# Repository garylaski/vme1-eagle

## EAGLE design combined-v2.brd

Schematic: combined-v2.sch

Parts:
3V3_D1, 9VDD1: SMD2; SMD1,27-2,54
10KPOT1_PAN1, 10KPOT1_PAN2, 10KPOT1_PAN3, 10KPOT1_PAN4, 10POT1_COMP1, 10POT1_COMP2, 10POT1_COMP3, 10POT1_COMP5, 10POT2_COMP1, 10POT2_COMP2, 10POT2_COMP3, 10POT2_COMP5: MCP4131-503E/SN; SOIC127P599X175-8N
100POT1_COMP1, 100POT1_COMP2, 100POT1_COMP3, 100POT1_COMP5: MCP42100-I/P; DIP254P762X432-14
200POT1_COMP1, 200POT2_COMP1: MAX5419NETA+; SON65P300X300X80-9N
200POT1_COMP2, 200POT2_COMP2: MAX5419META+; SON65P300X300X80-9N
200POT1_COMP3, 200POT2_COMP3: MAX5419PETAT; SON65P300X300X80-9N
200POT1_COMP5, 200POT2_COMP5: MAX5419LETA+; SON65P300X300X80-9N
BCK_ADC1: SMD2; SMD1,27-2,54
C2, C5, C6, C8, C24, C25, C26, C27, C28, C29, C30, C31, C32, C34, C35, C36, C37, C39, C43, C46, C49, C55, C69, C71, C77, C78, C79, C80, C81, C82, C83, C84, C119, C120, C121, C122, C123, C124, C125, C126, C127, C129, C130, C131, C132, C134: 10uF; C0402
C3, C4, C33, C38, C68, C70, C73, C128, C133: 0.1uF; C0402
C7, C9, C22, C23, C103, C104, C117, C118: 0.047uF; C0402
C10, C11, C14, C15, C16, C17, C20, C21, C105, C106, C109, C110, C111, C112, C115, C116: 0.01uF; C0402
C12, C13, C18, C19, C107, C108, C113, C114: 0.068uF; C0402
C42, C45, C48, C54: 680pF; C0402
C44, C47, C50, C56: 1.5uF; C0402
C72, C74: 1uF; C0402
C75, C76: 15pF; C0402
CE_EQ1, CE_EQ2: SMD2; SMD1,27-2,54
CLK_ADC1: SMD2; SMD1,27-2,54
CS3, CS4, CS5, CS6: SMD2; SMD1,27-2,54
D2, D3, D4, D5, D16, D17, D18, D19, D20, D21, D22, D23, D24, D25, D26, D27, D28, D29, D30, D31, D32, D33, D34, D35, D36, D37, D38, D39, D40, D41, D42, D43, D44, D45, D46, D47, D48, D60, D61, D62, D63, D64, D65, D66, D67, D68, D69, D70: 1N4148W-TP; SOD123
DOUT_ADC1: SMD2; SMD1,27-2,54
GND1, GND2, GND3, GND5: SMD5; SMD2,54-5,08
GND4, GND6: SMD2; SMD1,27-2,54
GNDL1: SMD5; SMD2,54-5,08
GNDR1: SMD5; SMD2,54-5,08
IC2: PCM1865DBT; TSSOP-30
IN_COMP1, IN_COMP2, IN_COMP3, IN_COMP5: SMD5; SMD2,54-5,08
LRCK_ADC1: SMD2; SMD1,27-2,54
MUX2, MUX3: SMD2; SMD1,27-2,54
OPAMP1_COMP1, OPAMP1_COMP2, OPAMP1_COMP3, OPAMP1_COMP5, OPAMP1_MIX1, OPAMP1_PAN1, OPAMP1_PAN2, OPAMP1_PAN3, OPAMP1_PAN4, OPAMP2_COMP1, OPAMP2_COMP2, OPAMP2_COMP3, OPAMP2_COMP5, OPAMP3_COMP1, OPAMP3_COMP2, OPAMP3_COMP3, OPAMP3_COMP5, OPAMP4_COMP1, OPAMP4_COMP2, OPAMP4_COMP3, OPAMP4_COMP5: LM4562MAX/NOPB; SOIC127P599X175-8N
OUTL_MIX1: SMD5; SMD2,54-5,08
OUTR_MIX1: SMD5; SMD2,54-5,08
PAD1, PAD2, PAD3, PAD4, PAD5, PAD6, PAD7, PAD8, PAD9, PAD10, PAD11, PAD12, PAD13, PAD14, PAD15, PAD16: SMD2; SMD1,27-2,54
R5, R8, R9, R12, R14, R19, R21, R32, R34, R41, R42, R47, R49, R56, R57, R72, R74, R76, R80, R86, R88, R92, R101, R105, R110, R119, R123, R128, R155, R159, R164: 10k; R0402
R6, R15, R68, R82: 1M; R0402
R7, R10, R11, R13, R16, R17, R18, R20, R31, R33, R35, R36, R37, R38, R39, R40, R43, R46, R48, R50, R51, R52, R53, R54, R55, R58, R69, R70, R71, R73, R83, R84, R85, R87: 5k; R0402
R22: 17k; R0402
R44, R59: 50k; R0402
R45, R60, R65, R97, R115, R151: 1k; R0402
R63, R67, R75, R77, R78, R79, R89, R90, R91, R93, R94, R95, R99, R100, R102, R103, R104, R107, R108, R109, R111, R112, R113, R117, R118, R120, R121, R122, R125, R126, R127, R129, R130, R149, R153, R154, R156, R157, R158, R161, R162, R163, R165, R166: 100k; R0402
R64, R66, R96, R98, R114, R116, R150, R152: 470k; R0402
R81, R106, R124, R160: 20k; R0402
SCK1: SMD2; SMD1,27-2,54
SCL1, SCL2: SMD2; SMD1,27-2,54
SDA1, SDA2: SMD2; SMD1,27-2,54
SDI/O1: SMD2; SMD1,27-2,54
U2: LM4562MAX/NOPB; SOIC127P599X175-8N
U3, U4, U5, U11: TMUX1204DGSR; SOP50P490X110-10N
U$1, U$3: LC75281E; QFP80P1720X1720X270-64N
Y2: ECS-245.7-20-3X-EN-TR; XTAL_ECS-245.7-20-3X-EN-TR

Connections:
3V3A: C70.1, C71.1, IC2.8 (AVDD), U2.1 (OUT_A), U2.2 (NEG_A)
3V3D: C68.1, C69.1, IC2.13 (DVDD), IC2.14 (IOVDD)
+3V3: 3V3_D1.1, U3.5 (EN), U3.6 (VDD), U4.5 (EN), U4.6 (VDD), U5.5 (EN), U5.6 (VDD), U11.5 (EN), U11.6 (VDD)
BCK_ADC: BCK_ADC1.1, IC2.17 (BCK)
CLK_ADC: CLK_ADC1.1, IC2.15 (SCKI)
CS: CS6.1, U11.8 (D)
CS0: CS3.1, U3.8 (D)
CS0_COMP1: 100POT1_COMP1.1 (~CS), U3.2 (S1)
CS0_COMP2: 100POT1_COMP3.1 (~CS), U3.9 (S2)
CS0_COMP3: 100POT1_COMP2.1 (~CS), U3.4 (S3)
CS0_COMP4: 100POT1_COMP5.1 (~CS), U3.7 (S4)
CS1: CS4.1, U5.8 (D)
CS1_COMP1: 10POT1_COMP1.1 (!CS), U5.2 (S1)
CS1_COMP2: 10POT1_COMP3.1 (!CS), U5.9 (S2)
CS1_COMP3: 10POT1_COMP2.1 (!CS), U5.4 (S3)
CS1_COMP4: 10POT1_COMP5.1 (!CS), U5.7 (S4)
CS2: CS5.1, U4.8 (D)
CS2_COMP1: 10POT2_COMP1.1 (!CS), U4.2 (S1)
CS2_COMP2: 10POT2_COMP3.1 (!CS), U4.9 (S2)
CS2_COMP3: 10POT2_COMP2.1 (!CS), U4.4 (S3)
CS2_COMP4: 10POT2_COMP5.1 (!CS), U4.7 (S4)
CS_PAN1: 10KPOT1_PAN1.1 (!CS), U11.2 (S1)
CS_PAN2: 10KPOT1_PAN3.1 (!CS), U11.9 (S2)
CS_PAN3: 10KPOT1_PAN2.1 (!CS), U11.4 (S3)
CS_PAN4: 10KPOT1_PAN4.1 (!CS), U11.7 (S4)
DOUT_ADC: DOUT_ADC1.1, IC2.18 (DOUT)
EQ1_CE1: CE_EQ1.1, U$1.27 (CE)
EQ2_CE3: CE_EQ2.1, U$3.27 (CE)
GND: 10KPOT1_PAN1.4 (VSS), 10KPOT1_PAN2.4 (VSS), 10KPOT1_PAN3.4 (VSS), 10KPOT1_PAN4.4 (VSS), 10POT1_COMP1.4 (VSS), 10POT1_COMP2.4 (VSS), 10POT1_COMP3.4 (VSS), 10POT1_COMP5.4 (VSS), 10POT2_COMP1.4 (VSS), 10POT2_COMP2.4 (VSS), 10POT2_COMP3.4 (VSS), 10POT2_COMP5.4 (VSS), 100POT1_COMP1.4 (VSS), 100POT1_COMP2.4 (VSS), 100POT1_COMP3.4 (VSS), 100POT1_COMP5.4 (VSS), 200POT1_COMP1.5 (GND), 200POT1_COMP1.9 (EPAD), 200POT1_COMP2.5 (GND), 200POT1_COMP2.9 (EPAD), 200POT1_COMP3.5 (GND), 200POT1_COMP3.9 (EPAD), 200POT1_COMP5.5 (GND), 200POT1_COMP5.9 (EPAD), 200POT2_COMP1.4 (A0), 200POT2_COMP1.5 (GND), 200POT2_COMP1.9 (EPAD), 200POT2_COMP2.4 (A0), 200POT2_COMP2.5 (GND), 200POT2_COMP2.9 (EPAD), 200POT2_COMP3.4 (A0), 200POT2_COMP3.5 (GND), 200POT2_COMP3.9 (EPAD), 200POT2_COMP5.4 (A0), 200POT2_COMP5.5 (GND), 200POT2_COMP5.9 (EPAD), C28.2, C39.2, C68.2, C69.2, C70.2, C71.2, C72.2, C73.2, C74.2, C75.2, C76.2, C123.2, C134.2, GND1.1, GND2.1, GND3.1, GND4.1, GND5.1, GND6.1, GNDL1.1, GNDR1.1, IC2.7 (AGND), IC2.12 (DGND), IC2.25 (MS/AD), OPAMP1_COMP1.4 (V-), OPAMP1_COMP2.4 (V-), OPAMP1_COMP3.4 (V-), OPAMP1_COMP5.4 (V-), OPAMP1_MIX1.4 (V-), OPAMP1_PAN1.4 (V-), OPAMP1_PAN2.4 (V-), OPAMP1_PAN3.4 (V-), OPAMP1_PAN4.4 (V-), OPAMP2_COMP1.4 (V-), OPAMP2_COMP2.4 (V-), OPAMP2_COMP3.4 (V-), OPAMP2_COMP5.4 (V-), OPAMP3_COMP1.4 (V-), OPAMP3_COMP2.4 (V-), OPAMP3_COMP3.4 (V-), OPAMP3_COMP5.4 (V-), OPAMP4_COMP1.4 (V-), OPAMP4_COMP2.4 (V-), OPAMP4_COMP3.4 (V-), OPAMP4_COMP5.4 (V-), R5.1, R9.1, U2.4 (V-), U3.3 (GND), U4.3 (GND), U5.3 (GND), U11.3 (GND), U$1.21 (V_SS), U$1.28 (TEST), U$3.21 (V_SS), U$3.28 (TEST)
H1_COMP1: 200POT1_COMP1.8 (H), 200POT2_COMP1.8 (H), C44.1, OPAMP1_COMP1.6 (NEG_B), R66.1
H1_COMP2: 200POT1_COMP3.8 (H), 200POT2_COMP3.8 (H), C50.1, OPAMP1_COMP3.6 (NEG_B), R116.1
H1_COMP3: 200POT1_COMP2.8 (H), 200POT2_COMP2.8 (H), C47.1, OPAMP1_COMP2.6 (NEG_B), R98.1
H1_COMP4: 200POT1_COMP5.8 (H), 200POT2_COMP5.8 (H), C56.1, OPAMP1_COMP5.6 (NEG_B), R152.1
IN_COMP1: C43.2, IN_COMP1.1
IN_COMP2: C49.2, IN_COMP3.1
IN_COMP3: C46.2, IN_COMP2.1
IN_COMP4: C55.2, IN_COMP5.1
L1_COMP1: 200POT1_COMP1.6 (L), 200POT1_COMP1.7 (W), D19.1
L1_COMP2: 200POT1_COMP3.6 (L), 200POT1_COMP3.7 (W), D41.1
L1_COMP3: 200POT1_COMP2.6 (L), 200POT1_COMP2.7 (W), D30.1
L1_COMP4: 200POT1_COMP5.6 (L), 200POT1_COMP5.7 (W), D63.1
L2_COMP1: 200POT2_COMP1.6 (L), 200POT2_COMP1.7 (W), R94.2
L2_COMP2: 200POT2_COMP3.6 (L), 200POT2_COMP3.7 (W), R130.2
L2_COMP3: 200POT2_COMP2.6 (L), 200POT2_COMP2.7 (W), R112.2
L2_COMP4: 200POT2_COMP5.6 (L), 200POT2_COMP5.7 (W), R166.2
LRCK_ADC: IC2.16 (LRCK), LRCK_ADC1.1
MUX0: MUX2.1, U3.1 (A0), U4.1 (A0), U5.1 (A0), U11.1 (A0)
MUX1: MUX3.1, U3.10 (A1), U4.10 (A1), U5.10 (A1), U11.10 (A1)
unnamed: C2.2, R6.2, R7.2, R10.2
unnamed: C5.2, R15.2, R16.2, R17.2
unnamed: C7.1, U$1.1 (LLC1)
unnamed: C10.1, U$1.6 (LLMC1)
unnamed: C11.1, U$1.7 (LLMC4)
unnamed: C12.1, U$1.11 (LHMC1)
unnamed: C3.1, R45.2
unnamed: R32.1, R35.2, R39.2
unnamed: R32.2, R34.2, R41.2, R42.2, R43.1
unnamed: R31.2, R38.1, R42.1
unnamed: R33.2, R37.1, R41.1
unnamed: C13.1, U$1.12 (LHMC4)
unnamed: C14.1, U$1.16 (LHC1)
unnamed: C15.1, U$1.17 (LHC4)
unnamed: C16.1, U$1.32 (RHC4)
unnamed: C17.1, U$1.33 (RHC1)
unnamed: R34.1, R36.1, R40.2
unnamed: C4.1, R60.2
unnamed: R47.1, R50.2, R54.2
unnamed: R47.2, R49.2, R56.2, R57.2, R58.1
unnamed: R46.2, R53.1, R57.1
unnamed: R48.2, R52.1, R56.1
unnamed: R49.1, R51.1, R55.2
unnamed: C18.1, U$1.37 (RHMC4)
unnamed: C6.2, R68.2, R69.2, R70.2
unnamed: C19.1, U$1.38 (RHMC1)
unnamed: C8.2, R82.2, R83.2, R84.2
unnamed: C20.1, U$1.42 (RLMC4)
unnamed: C21.1, U$1.43 (RLMC1)
unnamed: C22.1, U$1.47 (RLC4)
unnamed: C23.1, U$1.48 (RLC1)
unnamed: C7.2, U$1.64 (LLC2)
unnamed: C9.2, C24.2, U$1.3 (LLC3)
unnamed: C24.1, U$1.4 (LLC5)
unnamed: C25.1, U$1.9 (LLMC5)
unnamed: C26.1, U$1.14 (LHMC5)
unnamed: C27.1, U$1.19 (LHC5)
unnamed: C28.1, C39.1, U$1.23 (V_REF)
unnamed: C29.1, U$1.30 (RHC5)
unnamed: C30.1, U$1.35 (RHMC5)
unnamed: C31.1, U$1.40 (RLMC5)
unnamed: C32.1, U$1.45 (RLC5)
unnamed: C33.1, U$1.50 (ROUT)
unnamed: C34.1, U$1.52 (RBOOS2)
unnamed: C35.1, U$1.55 (RCUT2)
unnamed: C36.1, U$1.59 (LCUT1)
unnamed: C37.1, U$1.62 (LBOOS1)
unnamed: C38.1, U$1.63 (LOUT)
unnamed: C10.2, U$1.5 (LLMC2)
unnamed: C11.2, C25.2, U$1.8 (LLMC3)
unnamed: C12.2, U$1.10 (LHMC2)
unnamed: C13.2, C26.2, U$1.13 (LHMC3)
unnamed: C14.2, U$1.15 (LHC2)
unnamed: C15.2, C27.2, U$1.18 (LHC3)
unnamed: C16.2, C29.2, U$1.31 (RHC3)
unnamed: C17.2, U$1.34 (RHC2)
unnamed: C18.2, C30.2, U$1.36 (RHMC3)
unnamed: C19.2, U$1.39 (RHMC2)
unnamed: C20.2, C31.2, U$1.41 (RLMC3)
unnamed: C21.2, U$1.44 (RLMC2)
unnamed: C22.2, C32.2, U$1.46 (RLC3)
unnamed: C23.2, U$1.49 (RLC2)
unnamed: C34.2, U$1.51 (RBOOS1)
unnamed: C35.2, U$1.54 (RCUT1)
unnamed: C36.2, U$1.58 (LCUT2)
unnamed: C37.2, U$1.61 (LBOOS2)
unnamed: C9.1, U$1.2 (LLC4)
unnamed: R9.2, R22.2, U2.3 (POS_A)
unnamed: R5.2, R8.2, U2.5 (POS_B)
unnamed: D16.2, D17.1
unnamed: D21.2, D22.1
unnamed: D20.2, D21.1
unnamed: C43.1, R91.2
unnamed: D24.2, D25.1
unnamed: D23.2, D24.1
unnamed: D27.2, D28.1
unnamed: D32.2, D33.1
unnamed: D31.2, D32.1
unnamed: C46.1, R109.2
unnamed: D35.2, D36.1
unnamed: D34.2, D35.1
unnamed: D38.2, D39.1
unnamed: D43.2, D44.1
unnamed: D42.2, D43.1
unnamed: C49.1, R127.2
unnamed: D46.2, D47.1
unnamed: D45.2, D46.1
unnamed: D60.2, D61.1
unnamed: D65.2, D66.1
unnamed: D64.2, D65.1
unnamed: C55.1, R163.2
unnamed: D68.2, D69.1
unnamed: D67.2, D68.1
unnamed: C72.1, IC2.6 (VREF)
unnamed: C73.1, C74.1, IC2.11 (LDO)
unnamed: C75.1, IC2.9 (XO), Y2.2
unnamed: C76.1, IC2.10 (XI), Y2.1
unnamed: C84.2, IC2.1 (VINL2/VIN1M)
unnamed: C77.2, IC2.2 (VINR2/VIN2M)
unnamed: C103.1, U$3.1 (LLC1)
unnamed: C105.1, U$3.6 (LLMC1)
unnamed: C106.1, U$3.7 (LLMC4)
unnamed: C81.2, IC2.3 (VINL1/VIN1P)
unnamed: C107.1, U$3.11 (LHMC1)
unnamed: C78.2, IC2.4 (VINR1/VIN2P)
unnamed: C79.2, IC2.29 (VINL3/VIN4P)
unnamed: C83.2, IC2.28 (VINR4/VIN3M)
unnamed: C80.2, IC2.27 (VINL4/VIN4M)
unnamed: C108.1, U$3.12 (LHMC4)
unnamed: C109.1, U$3.16 (LHC1)
unnamed: C110.1, U$3.17 (LHC4)
unnamed: C111.1, U$3.32 (RHC4)
unnamed: C112.1, U$3.33 (RHC1)
unnamed: C113.1, U$3.37 (RHMC4)
unnamed: C114.1, U$3.38 (RHMC1)
unnamed: C115.1, U$3.42 (RLMC4)
unnamed: C116.1, U$3.43 (RLMC1)
unnamed: C117.1, U$3.47 (RLC4)
unnamed: C118.1, U$3.48 (RLC1)
unnamed: C103.2, U$3.64 (LLC2)
unnamed: C104.2, C119.2, U$3.3 (LLC3)
unnamed: C119.1, U$3.4 (LLC5)
unnamed: C120.1, U$3.9 (LLMC5)
unnamed: C121.1, U$3.14 (LHMC5)
unnamed: C122.1, U$3.19 (LHC5)
unnamed: C123.1, C134.1, U$3.23 (V_REF)
unnamed: C124.1, U$3.30 (RHC5)
unnamed: C125.1, U$3.35 (RHMC5)
unnamed: C126.1, U$3.40 (RLMC5)
unnamed: C127.1, U$3.45 (RLC5)
unnamed: C128.1, U$3.50 (ROUT)
unnamed: C129.1, U$3.52 (RBOOS2)
unnamed: C130.1, U$3.55 (RCUT2)
unnamed: C131.1, U$3.59 (LCUT1)
unnamed: C132.1, U$3.62 (LBOOS1)
unnamed: C133.1, U$3.63 (LOUT)
unnamed: C105.2, U$3.5 (LLMC2)
unnamed: C106.2, C120.2, U$3.8 (LLMC3)
unnamed: C107.2, U$3.10 (LHMC2)
unnamed: C108.2, C121.2, U$3.13 (LHMC3)
unnamed: C109.2, U$3.15 (LHC2)
unnamed: C110.2, C122.2, U$3.18 (LHC3)
unnamed: C111.2, C124.2, U$3.31 (RHC3)
unnamed: C112.2, U$3.34 (RHC2)
unnamed: C113.2, C125.2, U$3.36 (RHMC3)
unnamed: C114.2, U$3.39 (RHMC2)
unnamed: C115.2, C126.2, U$3.41 (RLMC3)
unnamed: C116.2, U$3.44 (RLMC2)
unnamed: C117.2, C127.2, U$3.46 (RLC3)
unnamed: C118.2, U$3.49 (RLC2)
unnamed: C129.2, U$3.51 (RBOOS1)
unnamed: C130.2, U$3.54 (RCUT1)
unnamed: C131.2, U$3.58 (LCUT2)
unnamed: C132.2, U$3.61 (LBOOS2)
unnamed: C104.1, U$3.2 (LLC4)
unnamed: C82.2, IC2.30 (VINR3/VIN3P)
unnamed: C42.1, D17.2, D18.1, D25.2, R65.1, R89.2
unnamed: C48.1, D39.2, D40.1, D47.2, R115.1, R125.2
unnamed: C45.1, D28.2, D29.1, D36.2, R97.1, R107.2
unnamed: C54.1, D61.2, D62.1, D69.2, R151.1, R161.2
NEG_A1_COMP1: C42.2, D16.1, D18.2, OPAMP1_COMP1.2 (NEG_A), R63.2
NEG_A1_COMP2: C48.2, D38.1, D40.2, OPAMP1_COMP3.2 (NEG_A), R113.2
NEG_A1_COMP3: C45.2, D27.1, D29.2, OPAMP1_COMP2.2 (NEG_A), R95.2
NEG_A1_COMP4: C54.2, D60.1, D62.2, OPAMP1_COMP5.2 (NEG_A), R149.2
NEG_A2_COMP1: OPAMP2_COMP1.2 (NEG_A), R67.2, R75.1
NEG_A2_COMP2: OPAMP2_COMP3.2 (NEG_A), R117.2, R118.1
NEG_A2_COMP3: OPAMP2_COMP2.2 (NEG_A), R99.2, R100.1
NEG_A2_COMP4: OPAMP2_COMP5.2 (NEG_A), R153.2, R154.1
NEG_A3_COMP1: OPAMP3_COMP1.2 (NEG_A), R77.1, R78.2
NEG_A3_COMP2: OPAMP3_COMP3.2 (NEG_A), R120.1, R121.2
NEG_A3_COMP3: OPAMP3_COMP2.2 (NEG_A), R102.1, R103.2
NEG_A3_COMP4: OPAMP3_COMP5.2 (NEG_A), R156.1, R157.2
NEG_A4_COMP1: OPAMP4_COMP1.2 (NEG_A), R79.2, R80.2
NEG_A4_COMP2: OPAMP4_COMP3.2 (NEG_A), R122.2, R123.2
NEG_A4_COMP3: OPAMP4_COMP2.2 (NEG_A), R104.2, R105.2
NEG_A4_COMP4: OPAMP4_COMP5.2 (NEG_A), R158.2, R159.2
NEG_A_MIX: OPAMP1_MIX1.2 (NEG_A), R43.2, R44.1
NEG_A_PAN1: OPAMP1_PAN1.2 (NEG_A), R71.1, R74.1
NEG_A_PAN2: OPAMP1_PAN3.2 (NEG_A), R85.1, R88.1
NEG_A_PAN3: OPAMP1_PAN2.2 (NEG_A), R11.1, R14.1
NEG_A_PAN4: OPAMP1_PAN4.2 (NEG_A), R18.1, R21.1
NEG_B2_COMP1: OPAMP2_COMP1.6 (NEG_B), OPAMP2_COMP1.7 (OUT_B), R93.2
NEG_B2_COMP2: OPAMP2_COMP3.6 (NEG_B), OPAMP2_COMP3.7 (OUT_B), R129.2
NEG_B2_COMP3: OPAMP2_COMP2.6 (NEG_B), OPAMP2_COMP2.7 (OUT_B), R111.2
NEG_B2_COMP4: OPAMP2_COMP5.6 (NEG_B), OPAMP2_COMP5.7 (OUT_B), R165.2
NEG_B3_COMP1: OPAMP3_COMP1.6 (NEG_B), R89.1, R90.2
NEG_B3_COMP2: OPAMP3_COMP3.6 (NEG_B), R125.1, R126.2
NEG_B3_COMP3: OPAMP3_COMP2.6 (NEG_B), R107.1, R108.2
NEG_B3_COMP4: OPAMP3_COMP5.6 (NEG_B), R161.1, R162.2
NEG_B4_COMP1: 100POT1_COMP1.5 (PB1), OPAMP4_COMP1.6 (NEG_B), R81.2
NEG_B4_COMP2: 100POT1_COMP3.5 (PB1), OPAMP4_COMP3.6 (NEG_B), R124.2
NEG_B4_COMP3: 100POT1_COMP2.5 (PB1), OPAMP4_COMP2.6 (NEG_B), R106.2
NEG_B4_COMP4: 100POT1_COMP5.5 (PB1), OPAMP4_COMP5.6 (NEG_B), R160.2
NEG_B_MIX: OPAMP1_MIX1.6 (NEG_B), R58.2, R59.1
NEG_B_PAN1: OPAMP1_PAN1.6 (NEG_B), R72.2, R73.2
NEG_B_PAN2: OPAMP1_PAN3.6 (NEG_B), R86.2, R87.2
NEG_B_PAN3: OPAMP1_PAN2.6 (NEG_B), R12.2, R13.2
NEG_B_PAN4: OPAMP1_PAN4.6 (NEG_B), R19.2, R20.2
OUT1_EQ1: C6.1, C33.2, PAD16.1
OUT1_EQ2: C5.1, C128.2, PAD14.1
OUT2_EQ1: C8.1, C38.2, PAD15.1
OUT2_EQ2: C2.1, C133.2, PAD13.1
OUTL_MIX1: C3.2, OUTL_MIX1.1
OUTL_PAN1: C79.1, OPAMP1_PAN1.1 (OUT_A), PAD3.1, R55.1, R74.2
OUTL_PAN2: C80.1, OPAMP1_PAN3.1 (OUT_A), PAD5.1, R31.1, R88.2
OUTL_PAN3: C78.1, OPAMP1_PAN2.1 (OUT_A), PAD1.1, R14.2, R46.1
OUTL_PAN4: C84.1, OPAMP1_PAN4.1 (OUT_A), PAD7.1, R21.2, R40.1
OUTR_MIX1: C4.2, OUTR_MIX1.1
OUTR_PAN1: C82.1, OPAMP1_PAN1.7 (OUT_B), PAD6.1, R33.1, R72.1
OUTR_PAN2: C83.1, OPAMP1_PAN3.7 (OUT_B), PAD4.1, R54.1, R86.1
OUTR_PAN3: C81.1, OPAMP1_PAN2.7 (OUT_B), PAD8.1, R12.1, R39.1
OUTR_PAN4: C77.1, OPAMP1_PAN4.7 (OUT_B), PAD2.1, R19.1, R48.1
OUT_A1_COMP1: OPAMP1_COMP1.1 (OUT_A), R65.2
OUT_A1_COMP2: OPAMP1_COMP3.1 (OUT_A), R115.2
OUT_A1_COMP3: OPAMP1_COMP2.1 (OUT_A), R97.2
OUT_A1_COMP4: OPAMP1_COMP5.1 (OUT_A), R151.2
OUT_A2_COMP1: 100POT1_COMP1.10 (PB0), OPAMP2_COMP1.1 (OUT_A), R75.2
OUT_A2_COMP2: 100POT1_COMP3.10 (PB0), OPAMP2_COMP3.1 (OUT_A), R118.2
OUT_A2_COMP3: 100POT1_COMP2.10 (PB0), OPAMP2_COMP2.1 (OUT_A), R100.2
OUT_A2_COMP4: 100POT1_COMP5.10 (PB0), OPAMP2_COMP5.1 (OUT_A), R154.2
OUT_A3_COMP1: D26.2, OPAMP3_COMP1.1 (OUT_A)
OUT_A3_COMP2: D48.2, OPAMP3_COMP3.1 (OUT_A)
OUT_A3_COMP3: D37.2, OPAMP3_COMP2.1 (OUT_A)
OUT_A3_COMP4: D70.2, OPAMP3_COMP5.1 (OUT_A)
OUT_A4_COMP1: OPAMP4_COMP1.1 (OUT_A), OPAMP4_COMP1.5 (POS_B), R78.1, R79.1
OUT_A4_COMP2: OPAMP4_COMP3.1 (OUT_A), OPAMP4_COMP3.5 (POS_B), R121.1, R122.1
OUT_A4_COMP3: OPAMP4_COMP2.1 (OUT_A), OPAMP4_COMP2.5 (POS_B), R103.1, R104.1
OUT_A4_COMP4: OPAMP4_COMP5.1 (OUT_A), OPAMP4_COMP5.5 (POS_B), R157.1, R158.1
OUT_A_MIX: OPAMP1_MIX1.1 (OUT_A), R44.2, R45.1
OUT_B1_COMP1: D19.2, OPAMP1_COMP1.7 (OUT_B)
OUT_B1_COMP2: D41.2, OPAMP1_COMP3.7 (OUT_B)
OUT_B1_COMP3: D30.2, OPAMP1_COMP2.7 (OUT_B)
OUT_B1_COMP4: D63.2, OPAMP1_COMP5.7 (OUT_B)
OUT_B3_COMP1: D20.1, OPAMP3_COMP1.7 (OUT_B), R90.1
OUT_B3_COMP2: D42.1, OPAMP3_COMP3.7 (OUT_B), R126.1
OUT_B3_COMP3: D31.1, OPAMP3_COMP2.7 (OUT_B), R108.1
OUT_B3_COMP4: D64.1, OPAMP3_COMP5.7 (OUT_B), R162.1
OUT_B_MIX: OPAMP1_MIX1.7 (OUT_B), R59.2, R60.1
OUT_COMP1: 100POT1_COMP1.6 (PW1), 100POT1_COMP1.7 (PA1), OPAMP4_COMP1.7 (OUT_B), PAD10.1, U$1.60 (LIN)
OUT_COMP2: 100POT1_COMP3.6 (PW1), 100POT1_COMP3.7 (PA1), OPAMP4_COMP3.7 (OUT_B), PAD9.1, U$1.53 (RIN)
OUT_COMP3: 100POT1_COMP2.6 (PW1), 100POT1_COMP2.7 (PA1), OPAMP4_COMP2.7 (OUT_B), PAD12.1, U$3.60 (LIN)
OUT_COMP4: 100POT1_COMP5.6 (PW1), 100POT1_COMP5.7 (PA1), OPAMP4_COMP5.7 (OUT_B), PAD11.1, U$3.53 (RIN)
P0A1_COMP1: 10POT1_COMP1.5 (P0A), R76.2
P0A1_COMP2: 10POT1_COMP3.5 (P0A), R119.2
P0A1_COMP3: 10POT1_COMP2.5 (P0A), R101.2
P0A1_COMP4: 10POT1_COMP5.5 (P0A), R155.2
P0A2_COMP1: 10POT2_COMP1.5 (P0A), R92.1
P0A2_COMP2: 10POT2_COMP3.5 (P0A), R128.1
P0A2_COMP3: 10POT2_COMP2.5 (P0A), R110.1
P0A2_COMP4: 10POT2_COMP5.5 (P0A), R164.1
P0A_PAN1: 10KPOT1_PAN1.5 (P0A), R70.1, R71.2
P0A_PAN2: 10KPOT1_PAN3.5 (P0A), R84.1, R85.2
P0A_PAN3: 10KPOT1_PAN2.5 (P0A), R10.1, R11.2
P0A_PAN4: 10KPOT1_PAN4.5 (P0A), R17.1, R18.2
P0B_PAN1: 10KPOT1_PAN1.7 (P0B), R69.1, R73.1
P0B_PAN2: 10KPOT1_PAN3.7 (P0B), R83.1, R87.1
P0B_PAN3: 10KPOT1_PAN2.7 (P0B), R7.1, R13.1
P0B_PAN4: 10KPOT1_PAN4.7 (P0B), R16.1, R20.1
P0W1_COMP1: 10POT1_COMP1.6 (P0W), R67.1
P0W1_COMP2: 10POT1_COMP3.6 (P0W), R117.1
P0W1_COMP3: 10POT1_COMP2.6 (P0W), R99.1
P0W1_COMP4: 10POT1_COMP5.6 (P0W), R153.1
P0W_PAN1: 10KPOT1_PAN1.6 (P0W), D2.1
P0W_PAN2: 10KPOT1_PAN3.6 (P0W), D4.1
P0W_PAN3: 10KPOT1_PAN2.6 (P0W), D3.1
P0W_PAN4: 10KPOT1_PAN4.6 (P0W), D5.1
POS_A1_COMP1: 100POT1_COMP1.9 (PW0), OPAMP1_COMP1.3 (POS_A)
POS_A1_COMP2: 100POT1_COMP3.9 (PW0), OPAMP1_COMP3.3 (POS_A)
POS_A1_COMP3: 100POT1_COMP2.9 (PW0), OPAMP1_COMP2.3 (POS_A)
POS_A1_COMP4: 100POT1_COMP5.9 (PW0), OPAMP1_COMP5.3 (POS_A)
POS_A2_COMP1: OPAMP2_COMP1.3 (POS_A), R64.2, R66.2
POS_A2_COMP2: OPAMP2_COMP3.3 (POS_A), R114.2, R116.2
POS_A2_COMP3: OPAMP2_COMP2.3 (POS_A), R96.2, R98.2
POS_A2_COMP4: OPAMP2_COMP5.3 (POS_A), R150.2, R152.2
POS_A4_COMP1: D22.2, D23.1, OPAMP4_COMP1.3 (POS_A), R93.1
POS_A4_COMP2: D44.2, D45.1, OPAMP4_COMP3.3 (POS_A), R129.1
POS_A4_COMP3: D33.2, D34.1, OPAMP4_COMP2.3 (POS_A), R111.1
POS_A4_COMP4: D66.2, D67.1, OPAMP4_COMP5.3 (POS_A), R165.1
POS_B1_COMP1: D26.1, OPAMP1_COMP1.5 (POS_B), R77.2
POS_B1_COMP2: D48.1, OPAMP1_COMP3.5 (POS_B), R120.2
POS_B1_COMP3: D37.1, OPAMP1_COMP2.5 (POS_B), R102.2
POS_B1_COMP4: D70.1, OPAMP1_COMP5.5 (POS_B), R156.2
POS_B2_COMP1: 10POT2_COMP1.6 (P0W), 10POT2_COMP1.7 (P0B), OPAMP2_COMP1.5 (POS_B), R91.1
POS_B2_COMP2: 10POT2_COMP3.6 (P0W), 10POT2_COMP3.7 (P0B), OPAMP2_COMP3.5 (POS_B), R127.1
POS_B2_COMP3: 10POT2_COMP2.6 (P0W), 10POT2_COMP2.7 (P0B), OPAMP2_COMP2.5 (POS_B), R109.1
POS_B2_COMP4: 10POT2_COMP5.6 (P0W), 10POT2_COMP5.7 (P0B), OPAMP2_COMP5.5 (POS_B), R163.1
SCK: 10KPOT1_PAN1.2 (SCK), 10KPOT1_PAN2.2 (SCK), 10KPOT1_PAN3.2 (SCK), 10KPOT1_PAN4.2 (SCK), 10POT1_COMP1.2 (SCK), 10POT1_COMP2.2 (SCK), 10POT1_COMP3.2 (SCK), 10POT1_COMP5.2 (SCK), 10POT2_COMP1.2 (SCK), 10POT2_COMP2.2 (SCK), 10POT2_COMP3.2 (SCK), 10POT2_COMP5.2 (SCK), 100POT1_COMP1.2 (SCK), 100POT1_COMP2.2 (SCK), 100POT1_COMP3.2 (SCK), 100POT1_COMP5.2 (SCK), SCK1.1, U$1.25 (CL), U$3.25 (CL)
SCL: 200POT1_COMP1.2 (SCL), 200POT1_COMP2.2 (SCL), 200POT1_COMP3.2 (SCL), 200POT1_COMP5.2 (SCL), 200POT2_COMP1.2 (SCL), 200POT2_COMP2.2 (SCL), 200POT2_COMP3.2 (SCL), 200POT2_COMP5.2 (SCL), SCL1.1
SCL1: IC2.24 (MC/SCL), SCL2.1
SDA: 200POT1_COMP1.3 (SDA), 200POT1_COMP2.3 (SDA), 200POT1_COMP3.3 (SDA), 200POT1_COMP5.3 (SDA), 200POT2_COMP1.3 (SDA), 200POT2_COMP2.3 (SDA), 200POT2_COMP3.3 (SDA), 200POT2_COMP5.3 (SDA), SDA1.1
SDA1: IC2.23 (MOSI/SDA), SDA2.1
SDI/O: 10KPOT1_PAN1.3 (SDI/SDO), 10KPOT1_PAN2.3 (SDI/SDO), 10KPOT1_PAN3.3 (SDI/SDO), 10KPOT1_PAN4.3 (SDI/SDO), 10POT1_COMP1.3 (SDI/SDO), 10POT1_COMP2.3 (SDI/SDO), 10POT1_COMP3.3 (SDI/SDO), 10POT1_COMP5.3 (SDI/SDO), 10POT2_COMP1.3 (SDI/SDO), 10POT2_COMP2.3 (SDI/SDO), 10POT2_COMP3.3 (SDI/SDO), 10POT2_COMP5.3 (SDI/SDO), 100POT1_COMP1.3 (SI), 100POT1_COMP2.3 (SI), 100POT1_COMP3.3 (SI), 100POT1_COMP5.3 (SI), SDI/O1.1, U$1.26 (DI), U$3.26 (DI)
VDD: 9VDD1.1, OPAMP1_COMP1.8 (V+), OPAMP1_COMP2.8 (V+), OPAMP1_COMP3.8 (V+), OPAMP1_COMP5.8 (V+), OPAMP1_MIX1.8 (V+), OPAMP1_PAN1.8 (V+), OPAMP1_PAN2.8 (V+), OPAMP1_PAN3.8 (V+), OPAMP1_PAN4.8 (V+), OPAMP2_COMP1.8 (V+), OPAMP2_COMP2.8 (V+), OPAMP2_COMP3.8 (V+), OPAMP2_COMP5.8 (V+), OPAMP3_COMP1.8 (V+), OPAMP3_COMP2.8 (V+), OPAMP3_COMP3.8 (V+), OPAMP3_COMP5.8 (V+), OPAMP4_COMP1.8 (V+), OPAMP4_COMP2.8 (V+), OPAMP4_COMP3.8 (V+), OPAMP4_COMP5.8 (V+), R8.1, R22.1, R76.1, R101.1, R119.1, R155.1, U2.8 (V+), U$1.22 (V_DD), U$3.22 (V_DD)
VREF: 10KPOT1_PAN1.8 (VDD), 10KPOT1_PAN2.8 (VDD), 10KPOT1_PAN3.8 (VDD), 10KPOT1_PAN4.8 (VDD), 10POT1_COMP1.7 (P0B), 10POT1_COMP1.8 (VDD), 10POT1_COMP2.7 (P0B), 10POT1_COMP2.8 (VDD), 10POT1_COMP3.7 (P0B), 10POT1_COMP3.8 (VDD), 10POT1_COMP5.7 (P0B), 10POT1_COMP5.8 (VDD), 10POT2_COMP1.8 (VDD), 10POT2_COMP2.8 (VDD), 10POT2_COMP3.8 (VDD), 10POT2_COMP5.8 (VDD), 100POT1_COMP1.8 (PA0), 100POT1_COMP1.11 (~RS), 100POT1_COMP1.12 (~SHDN), 100POT1_COMP1.14 (VDD), 100POT1_COMP2.8 (PA0), 100POT1_COMP2.11 (~RS), 100POT1_COMP2.12 (~SHDN), 100POT1_COMP2.14 (VDD), 100POT1_COMP3.8 (PA0), 100POT1_COMP3.11 (~RS), 100POT1_COMP3.12 (~SHDN), 100POT1_COMP3.14 (VDD), 100POT1_COMP5.8 (PA0), 100POT1_COMP5.11 (~RS), 100POT1_COMP5.12 (~SHDN), 100POT1_COMP5.14 (VDD), 200POT1_COMP1.1 (VDD), 200POT1_COMP1.4 (A0), 200POT1_COMP2.1 (VDD), 200POT1_COMP2.4 (A0), 200POT1_COMP3.1 (VDD), 200POT1_COMP3.4 (A0), 200POT1_COMP5.1 (VDD), 200POT1_COMP5.4 (A0), 200POT2_COMP1.1 (VDD), 200POT2_COMP2.1 (VDD), 200POT2_COMP3.1 (VDD), 200POT2_COMP5.1 (VDD), C44.2, C47.2, C50.2, C56.2, D2.2, D3.2, D4.2, D5.2, OPAMP1_MIX1.3 (POS_A), OPAMP1_MIX1.5 (POS_B), OPAMP1_PAN1.3 (POS_A), OPAMP1_PAN1.5 (POS_B), OPAMP1_PAN2.3 (POS_A), OPAMP1_PAN2.5 (POS_B), OPAMP1_PAN3.3 (POS_A), OPAMP1_PAN3.5 (POS_B), OPAMP1_PAN4.3 (POS_A), OPAMP1_PAN4.5 (POS_B), OPAMP3_COMP1.3 (POS_A), OPAMP3_COMP1.5 (POS_B), OPAMP3_COMP2.3 (POS_A), OPAMP3_COMP2.5 (POS_B), OPAMP3_COMP3.3 (POS_A), OPAMP3_COMP3.5 (POS_B), OPAMP3_COMP5.3 (POS_A), OPAMP3_COMP5.5 (POS_B), R6.1, R15.1, R35.1, R36.2, R37.2, R38.2, R50.1, R51.2, R52.2, R53.2, R63.1, R64.1, R68.1, R80.1, R81.1, R82.1, R92.2, R94.1, R95.1, R96.1, R105.1, R106.1, R110.2, R112.1, R113.1, R114.1, R123.1, R124.1, R128.2, R130.1, R149.1, R150.1, R159.1, R160.1, R164.2, R166.1, U2.6 (NEG_B), U2.7 (OUT_B)

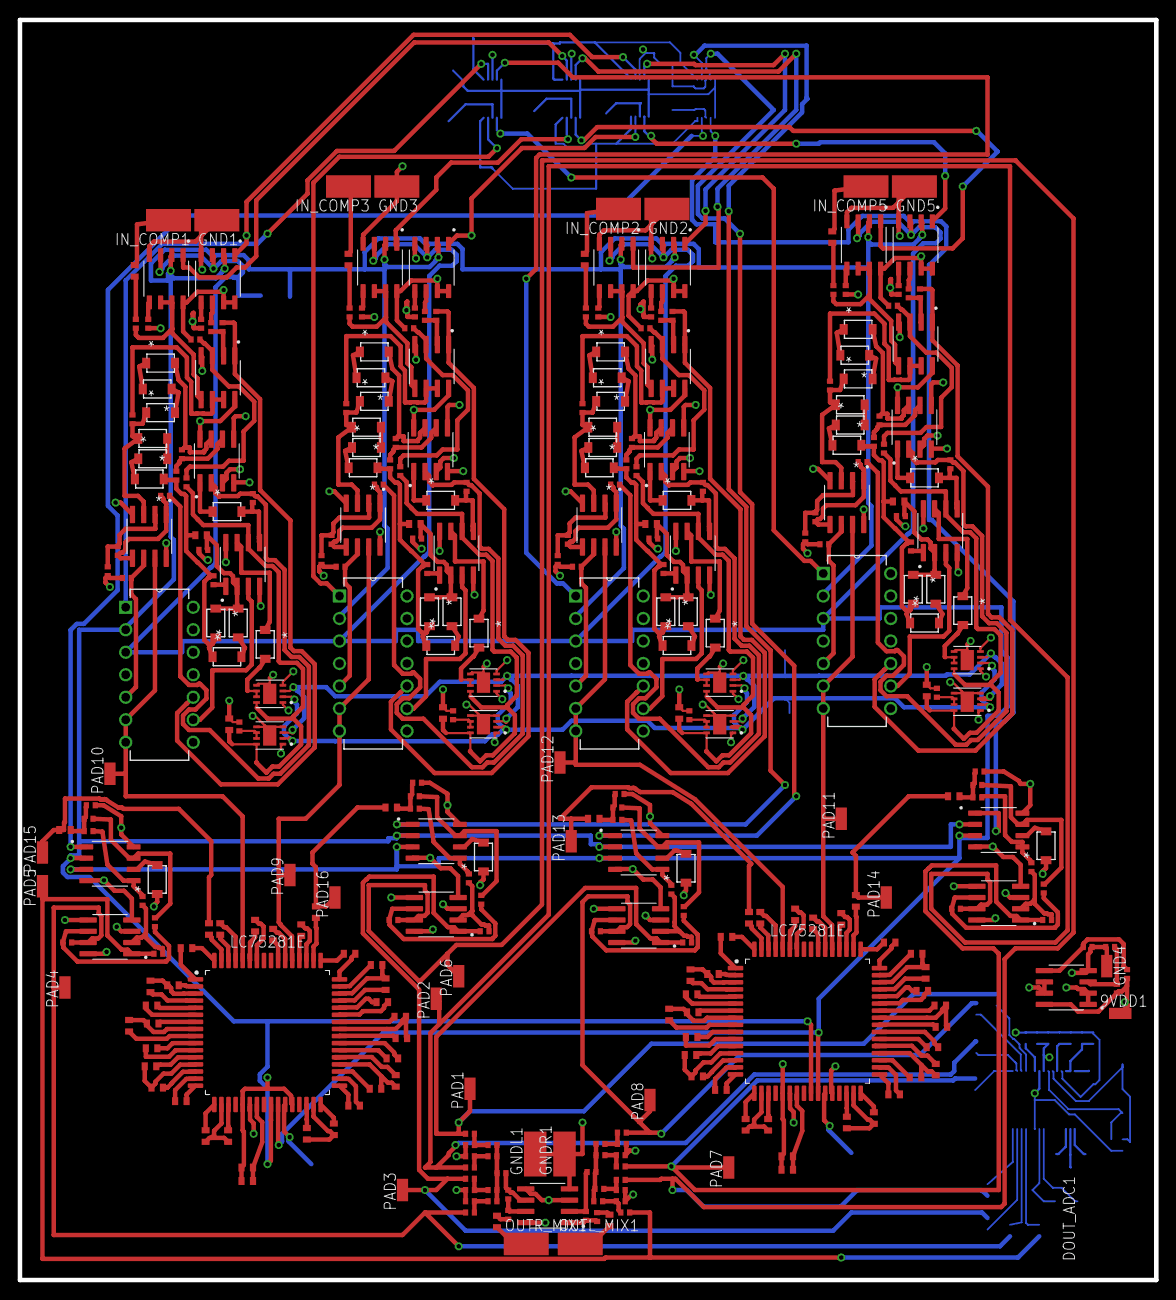
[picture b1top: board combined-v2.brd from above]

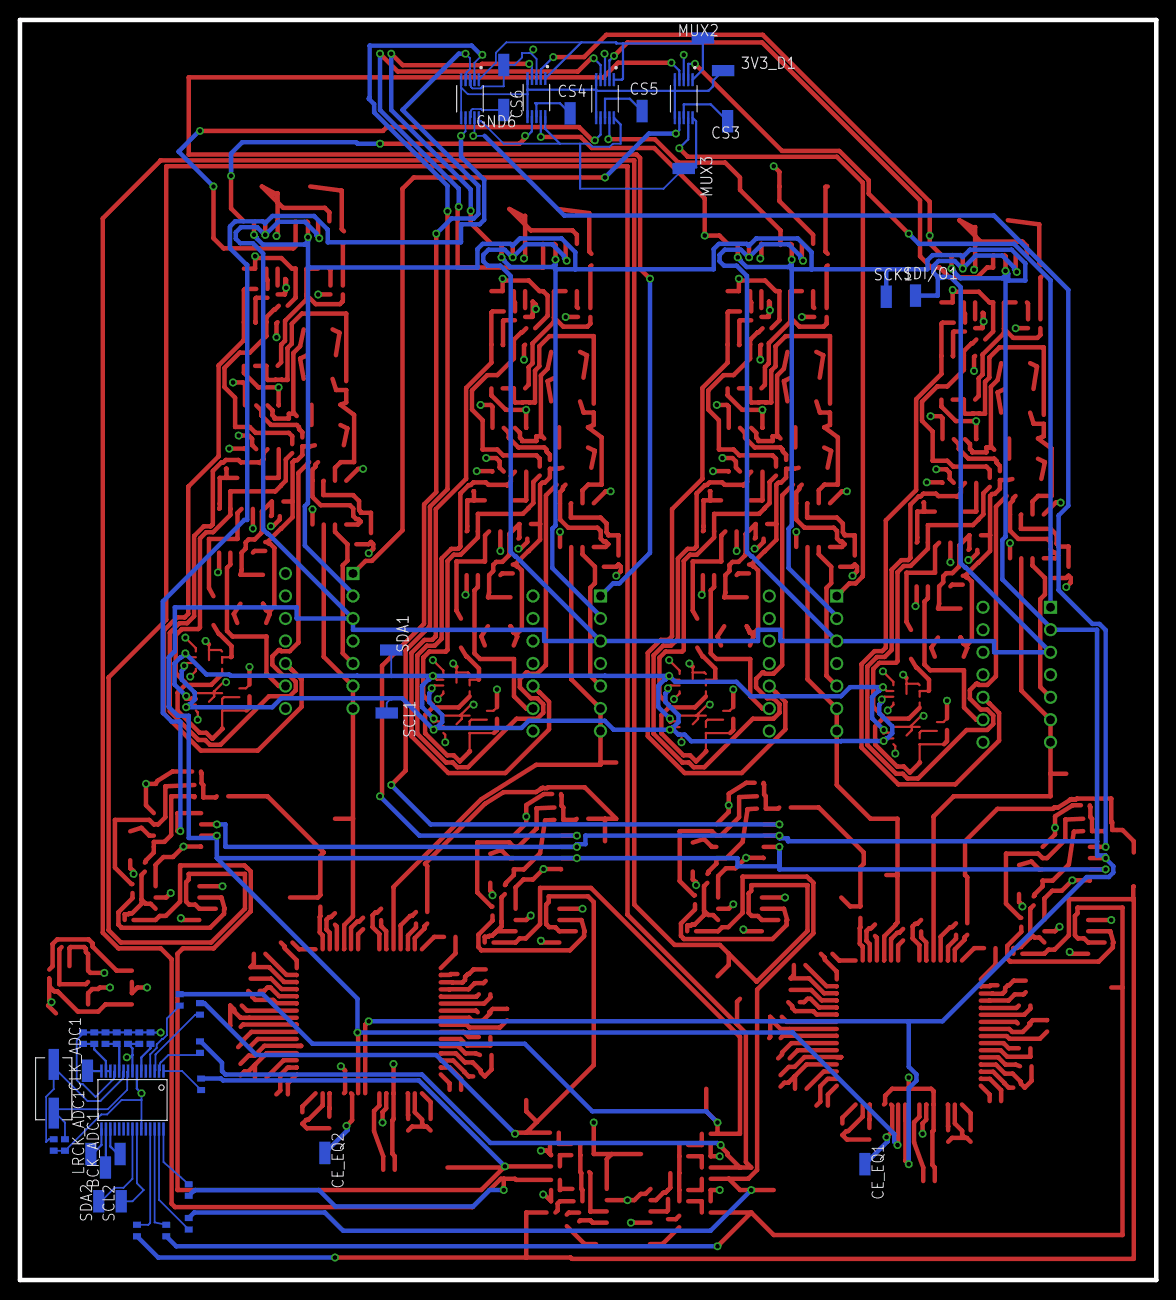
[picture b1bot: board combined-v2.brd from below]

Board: 4 copper layers, 128.3 x 142.2 mm, 385 parts (43 on the bottom side), 342 nets.

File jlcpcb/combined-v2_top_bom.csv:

Comment,Designator,Footprint,LCSC Part #
0.1uF,9VDD1 GND1 GND2 GND3 GND4 GND5 GNDL1 GNDR1 IN_COMP1 IN_COMP2 IN_COMP3 IN_COMP5 OUTL_MIX1 OUTR_MIX1 PAD1 PAD2 PAD3 PAD4 PAD5 PAD6 PAD7 PAD8 PAD9 PAD10 PAD11 PAD12 PAD13 PAD14 PAD15 PAD16 C3 C4 C33 C38 C128 C133,C0402,
0.01uF,C10 C11 C14 C15 C16 C17 C20 C21 C105 C106 C109 C110 C111 C112 C115 C116,C0402,
0.047uF,C7 C9 C22 C23 C103 C104 C117 C118,C0402,
0.068uF,C12 C13 C18 C19 C107 C108 C113 C114,C0402,
1.5uF,C44 C47 C50 C56,C0402,
1.7k,R22,R0402,
1M,R6 R15 R68 R82,R0402,
1N4148W-TP,D2 D3 D4 D5 D16 D17 D18 D19 D20 D21 D22 D23 D24 D25 D26 D27 D28 D29 D30 D31 D32 D33 D34 D35 D36 D37 D38 D39 D40 D41 D42 D43 D44 D45 D46 D47 D48 D60 D61 D62 D63 D64 D65 D66 D67 D68 D69 D70,SOD123,
1k,R5 R8 R9 R45 R60 R65 R97 R115 R151,R0402,
5k,R7 R10 R11 R13 R16 R17 R18 R20 R31 R33 R35 R36 R37 R38 R39 R40 R43 R46 R48 R50 R51 R52 R53 R54 R55 R58 R69 R70 R71 R73 R83 R84 R85 R87,R0402,
10k,R12 R14 R19 R21 R32 R34 R41 R42 R47 R49 R56 R57 R72 R74 R76 R80 R86 R88 R92 R101 R105 R110 R119 R123 R128 R155 R159 R164,R0402,
10uF,C2 C5 C6 C8 C24 C25 C26 C27 C28 C29 C30 C31 C32 C34 C35 C36 C37 C39 C43 C46 C49 C55 C119 C120 C121 C122 C123 C124 C125 C126 C127 C129 C130 C131 C132 C134,C0402,
20k,R81 R106 R124 R160,R0402,
50k,R44 R59,R0402,
100k,R63 R67 R75 R77 R78 R79 R89 R90 R91 R93 R94 R95 R99 R100 R102 R103 R104 R107 R108 R109 R111 R112 R113 R117 R118 R120 R121 R122 R125 R126 R127 R129 R130 R149 R153 R154 R156 R157 R158 R161 R162 R163 R165 R166,R0402,
470k,R64 R66 R96 R98 R114 R116 R150 R152,R0402,
680pF,C42 C45 C48 C54,C0402,
LC75281E,U$1 U$3,QFP80P1720X1720X270-64N,
LM4562MAX/NOPB,OPAMP1_COMP1 OPAMP1_COMP2 OPAMP1_COMP3 OPAMP1_COMP5 OPAMP1_MIX1 OPAMP1_PAN1 OPAMP1_PAN2 OPAMP1_PAN3 OPAMP1_PAN4 OPAMP2_COMP1 OPAMP2_COMP2 OPAMP2_COMP3 OPAMP2_COMP5 OPAMP3_COMP1 OPAMP3_COMP2 OPAMP3_COMP3 OPAMP3_COMP5 OPAMP4_COMP1 OPAMP4_COMP2 OPAMP4_COMP3 OPAMP4_COMP5 U2,SOIC127P599X175-8N,
MAX5419LETA+,200POT1_COMP5 200POT2_COMP5,SON65P300X300X80-9N,
MAX5419META+,200POT1_COMP2 200POT2_COMP2,SON65P300X300X80-9N,
MAX5419NETA+,200POT1_COMP1 200POT2_COMP1,SON65P300X300X80-9N,
MAX5419PETAT,200POT1_COMP3 200POT2_COMP3,SON65P300X300X80-9N,
MCP4131-503E/SN,10KPOT1_PAN1 10KPOT1_PAN2 10KPOT1_PAN3 10KPOT1_PAN4 10POT1_COMP1 10POT1_COMP2 10POT1_COMP3 10POT1_COMP5 10POT2_COMP1 10POT2_COMP2 10POT2_COMP3 10POT2_COMP5,SOIC127P599X175-8N,

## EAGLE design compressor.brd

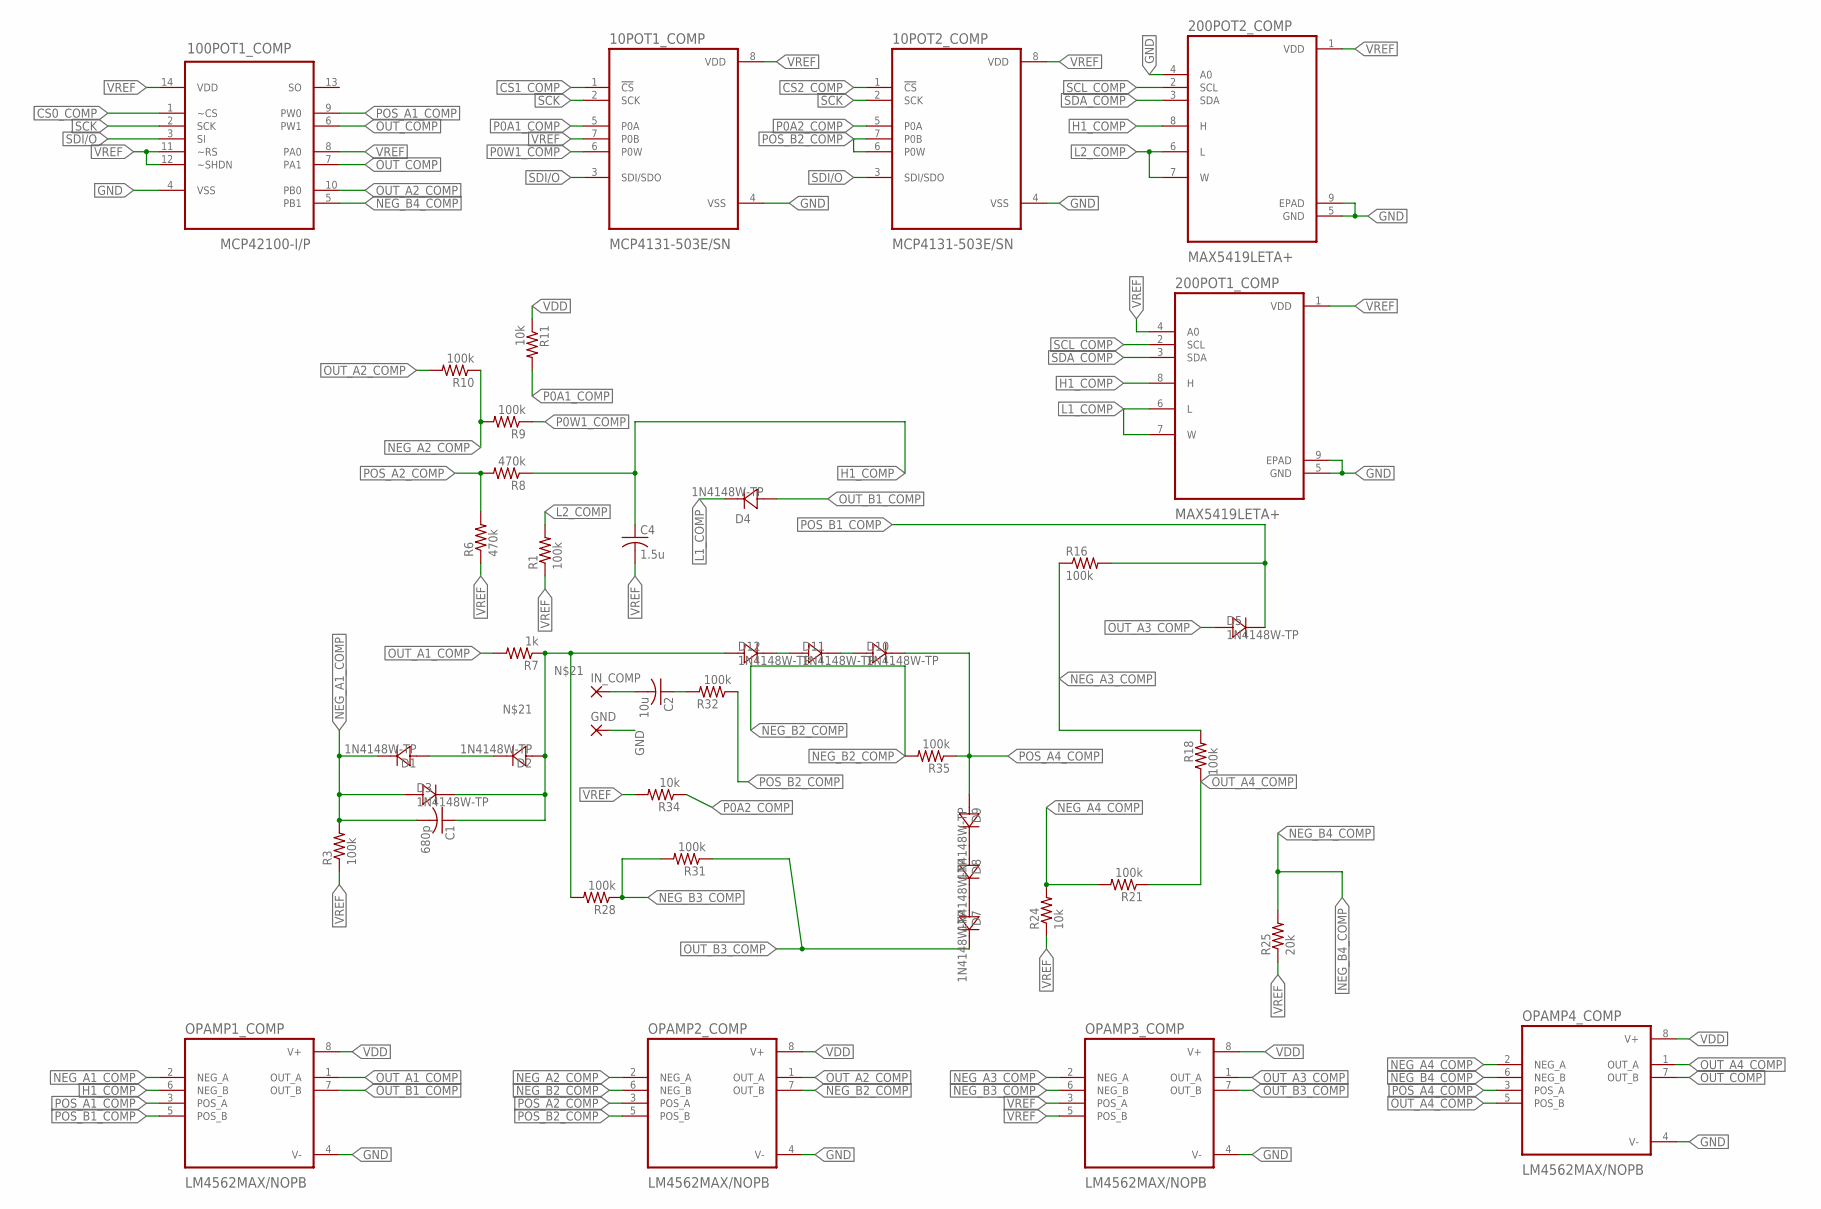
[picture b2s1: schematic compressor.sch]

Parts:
10POT1_COMP, 10POT2_COMP: MCP4131-503E/SN; SOIC127P599X175-8N
100POT1_COMP: MCP42100-I/P; DIP254P762X432-14
200POT1_COMP, 200POT2_COMP: MAX5419LETA+; SON65P300X300X80-9N
C1: 680p; C0402
C2: 10u; C0402
C4: 1.5u; C0402
D1, D2, D3, D4, D5, D7, D8, D9, D10, D11, D12: 1N4148W-TP; SOD123
GND: SMD5; SMD2,54-5,08
IN_COMP: SMD5; SMD2,54-5,08
OPAMP1_COMP, OPAMP2_COMP, OPAMP3_COMP, OPAMP4_COMP: LM4562MAX/NOPB; SOIC127P599X175-8N
R1, R3, R9, R10, R16, R18, R21, R28, R31, R32, R35: 100k; R0402
R6, R8: 470k; R0402
R7: 1k; R0402
R11, R24, R34: 10k; R0402
R25: 20k; R0402

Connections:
CS0_COMP: 100POT1_COMP.1 (~CS)
CS1_COMP: 10POT1_COMP.1 (!CS)
CS2_COMP: 10POT2_COMP.1 (!CS)
GND: 10POT1_COMP.4 (VSS), 10POT2_COMP.4 (VSS), 100POT1_COMP.4 (VSS), 200POT1_COMP.5 (GND), 200POT1_COMP.9 (EPAD), 200POT2_COMP.4 (A0), 200POT2_COMP.5 (GND), 200POT2_COMP.9 (EPAD), GND.1, OPAMP1_COMP.4 (V-), OPAMP2_COMP.4 (V-), OPAMP3_COMP.4 (V-), OPAMP4_COMP.4 (V-)
H1_COMP: 200POT1_COMP.8 (H), 200POT2_COMP.8 (H), C4.1, OPAMP1_COMP.6 (NEG_B), R8.1
IN_COMP: C2.2, IN_COMP.1
L1_COMP: 200POT1_COMP.6 (L), 200POT1_COMP.7 (W), D4.C
L2_COMP: 200POT2_COMP.6 (L), 200POT2_COMP.7 (W), R1.2
unnamed: D1.A, D2.C
unnamed: C1.1, D2.A, D3.C, D12.A, R7.1, R28.2
unnamed: D8.A, D9.C
unnamed: D7.A, D8.C
unnamed: C2.1, R32.2
unnamed: D11.A, D12.C
unnamed: D10.A, D11.C
NEG_A1_COMP: C1.2, D1.C, D3.A, OPAMP1_COMP.2 (NEG_A), R3.2
NEG_A2_COMP: OPAMP2_COMP.2 (NEG_A), R9.2, R10.1
NEG_A3_COMP: OPAMP3_COMP.2 (NEG_A), R16.1, R18.2
NEG_A4_COMP: OPAMP4_COMP.2 (NEG_A), R21.2, R24.2
NEG_B2_COMP: OPAMP2_COMP.6 (NEG_B), OPAMP2_COMP.7 (OUT_B), R35.2
NEG_B3_COMP: OPAMP3_COMP.6 (NEG_B), R28.1, R31.2
NEG_B4_COMP: 100POT1_COMP.5 (PB1), OPAMP4_COMP.6 (NEG_B), R25.2
OUT_A1_COMP: OPAMP1_COMP.1 (OUT_A), R7.2
OUT_A2_COMP: 100POT1_COMP.10 (PB0), OPAMP2_COMP.1 (OUT_A), R10.2
OUT_A3_COMP: D5.A, OPAMP3_COMP.1 (OUT_A)
OUT_A4_COMP: OPAMP4_COMP.1 (OUT_A), OPAMP4_COMP.5 (POS_B), R18.1, R21.1
OUT_B1_COMP: D4.A, OPAMP1_COMP.7 (OUT_B)
OUT_B3_COMP: D7.C, OPAMP3_COMP.7 (OUT_B), R31.1
OUT_COMP: 100POT1_COMP.6 (PW1), 100POT1_COMP.7 (PA1), OPAMP4_COMP.7 (OUT_B)
P0A1_COMP: 10POT1_COMP.5 (P0A), R11.2
P0A2_COMP: 10POT2_COMP.5 (P0A), R34.1
P0W1_COMP: 10POT1_COMP.6 (P0W), R9.1
POS_A1_COMP: 100POT1_COMP.9 (PW0), OPAMP1_COMP.3 (POS_A)
POS_A2_COMP: OPAMP2_COMP.3 (POS_A), R6.2, R8.2
POS_A4_COMP: D9.A, D10.C, OPAMP4_COMP.3 (POS_A), R35.1
POS_B1_COMP: D5.C, OPAMP1_COMP.5 (POS_B), R16.2
POS_B2_COMP: 10POT2_COMP.6 (P0W), 10POT2_COMP.7 (P0B), OPAMP2_COMP.5 (POS_B), R32.1
SCK: 10POT1_COMP.2 (SCK), 10POT2_COMP.2 (SCK), 100POT1_COMP.2 (SCK)
SCL_COMP: 200POT1_COMP.2 (SCL), 200POT2_COMP.2 (SCL)
SDA_COMP: 200POT1_COMP.3 (SDA), 200POT2_COMP.3 (SDA)
SDI/O: 10POT1_COMP.3 (SDI/SDO), 10POT2_COMP.3 (SDI/SDO), 100POT1_COMP.3 (SI)
VDD: OPAMP1_COMP.8 (V+), OPAMP2_COMP.8 (V+), OPAMP3_COMP.8 (V+), OPAMP4_COMP.8 (V+), R11.1
VREF: 10POT1_COMP.7 (P0B), 10POT1_COMP.8 (VDD), 10POT2_COMP.8 (VDD), 100POT1_COMP.8 (PA0), 100POT1_COMP.11 (~RS), 100POT1_COMP.12 (~SHDN), 100POT1_COMP.14 (VDD), 200POT1_COMP.1 (VDD), 200POT1_COMP.4 (A0), 200POT2_COMP.1 (VDD), C4.2, OPAMP3_COMP.3 (POS_A), OPAMP3_COMP.5 (POS_B), R1.1, R3.1, R6.1, R24.1, R25.1, R34.2

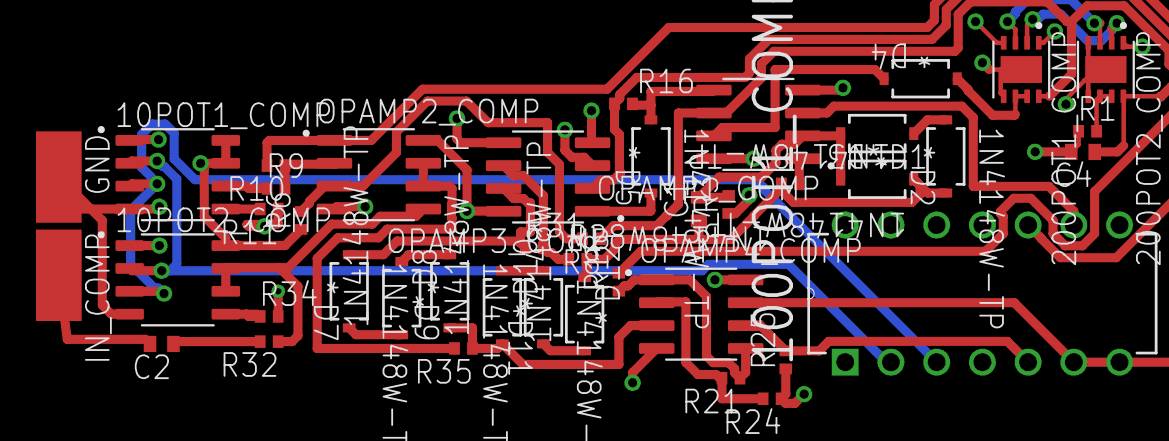
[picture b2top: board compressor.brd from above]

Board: 4 copper layers, 43 parts (0 on the bottom side), 40 nets.
